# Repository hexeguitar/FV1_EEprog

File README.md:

FV1 EEProg
==========

Expansion board used in conjunction with an EZ-USB FX2LP (LCSOFT version) Cypress CY7C68013A dev board (source: ebay)
to create an EEPROM programmer that works directly within the SpinAsm software. Idea based on FV-1 Dev board.

*** DOES NOT INVOLVE COPYING THE ORIGINAL FIRMWARE ***

The trick is to force a new hardware to be enumerated as FV-1 Dev board, after being detected by the SpinAsm software the firmware is uploaded via USB into the RAM of the CY7C68013A microcontroller.

The EZ-USB FX2LP board requires a small modification using an external I2C EEPROM programmer, like i.e. PicKit2:
The onboard 24LC128 EEPROM needs to be erased and written with the following sequence of bytes starting from the address 0x00:

C0 79 18 01 10 00 00 00

If you don't have any other EEPROM programmer the same task could be done using the Cypress CyConsole program (part of the Cypress Suite USC 3.4.7).

The jumper J1 should be installed, setting the EEPROM I2C address to 0xA2.

Here is how it works:
after plugging the usb cable, the cypress chip looks at the I2C bus for an EEPROM at address 0xA0 to read the VID and PID and send them back to the PC.
Normally, if the programmer is connected to any FV1 based device, it would read the first bytes of the EEPROM storing the dsp program (it's address is 0xA0).
That's why the I2C bus has to be disconnected from the target after plugging the programmer into the USB. That is the job for the daughter board, consisting of a 4066
quad switch controlled from the PA0 line. It's turned on only after a successful enumeration opening up the I2C bus to the target.
If the MCU doesn't find any EEPROM at 0xA0 it looks if there is anything at 0xA2 and finds the onboard 24LC128 EEPROM and stored VID&PID there.

After the successful enumeration and detection the RED led goes on showing the programmer is online and ready to work.
SpinAsm can directly upload the new firmware into the target eeprom and reset the dsp if necessary.

Automatic resetting the DSP after firmware upload:
this feature is done by quickly changing the T0 line (internal/external set of programs), which results in rereading the current DSP program.
In order to make a use of it in your application do not tie up the T0 line directly to the VDD (3.3V), but use a 10k pull up resistor. 

*** UPDATE 10.2019 ***
I have updated the project to work with the newer CY7C68013A dev boards.

Here is the link to the OSH Park project:

https://oshpark.com/shared_projects/5Jfe9GrT

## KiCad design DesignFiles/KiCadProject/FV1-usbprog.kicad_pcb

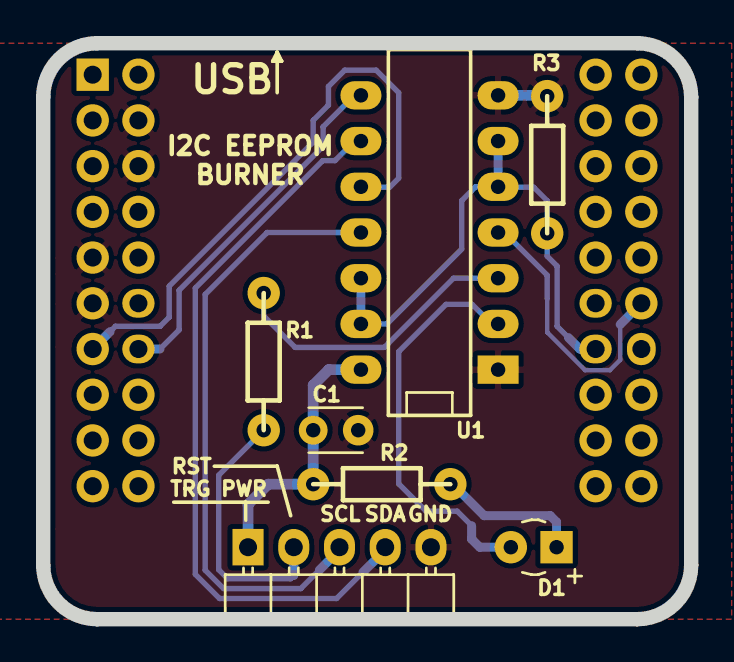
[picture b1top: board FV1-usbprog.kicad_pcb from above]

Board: 2 copper layers, 36.0 x 32.0 mm, 8 parts (0 on the bottom side), 12 nets.

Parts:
C1: 100n; C_Disc_D3_P2.5
D1: LED; Diode_LED_3mm_round_vertical
P1: PROG_BUF; Pin_Header_Angled_1x05
R1: 330R; RC03
R2, R3: 2k2; RC03
U1: 74LV4066; DIP-14__300_ELL
U2: CY7C68013A_dev_kit

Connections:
/DSP_RESET: U1.4, U2.29
/DSP_RST_BUF: P1.4, R1.2
/PROG_EN: R3.1, U1.5, U1.6, U1.12, U1.13, U2.28
/SCL_BUF: P1.3, U1.11
/SDA_BUF: P1.2, U1.9
/TRG_PWR: C1.1, P1.5, R2.1, U1.14
GND: C1.2, P1.1, R3.2, U1.1, U1.7, U2.4, U2.6, U2.9, U2.11
unnamed: D1.1, R2.2
unnamed: D1.2, U1.2
unnamed: R1.1, U1.3
unnamed: U1.8, U2.14
unnamed: U1.10, U2.13

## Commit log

2015-10-18 :octocat: Added .gitattributes & .gitignore files
2015-10-18 readme update
2019-10-18 fix typos
2019-10-18 Updated to kicad 5.1, improved compatibility with newer FX2LP boards
2019-10-18 updated OshPark link
2019-10-18 error fixed, cleanup, OshPark link update
2019-10-18 schematic update
2020-09-07 gitignore update
2020-09-07 License added

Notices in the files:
DesignFiles/KiCadProject/FV1-usbprog.kicad_pcb:
(c) 2015 www.hexeguitar.com
